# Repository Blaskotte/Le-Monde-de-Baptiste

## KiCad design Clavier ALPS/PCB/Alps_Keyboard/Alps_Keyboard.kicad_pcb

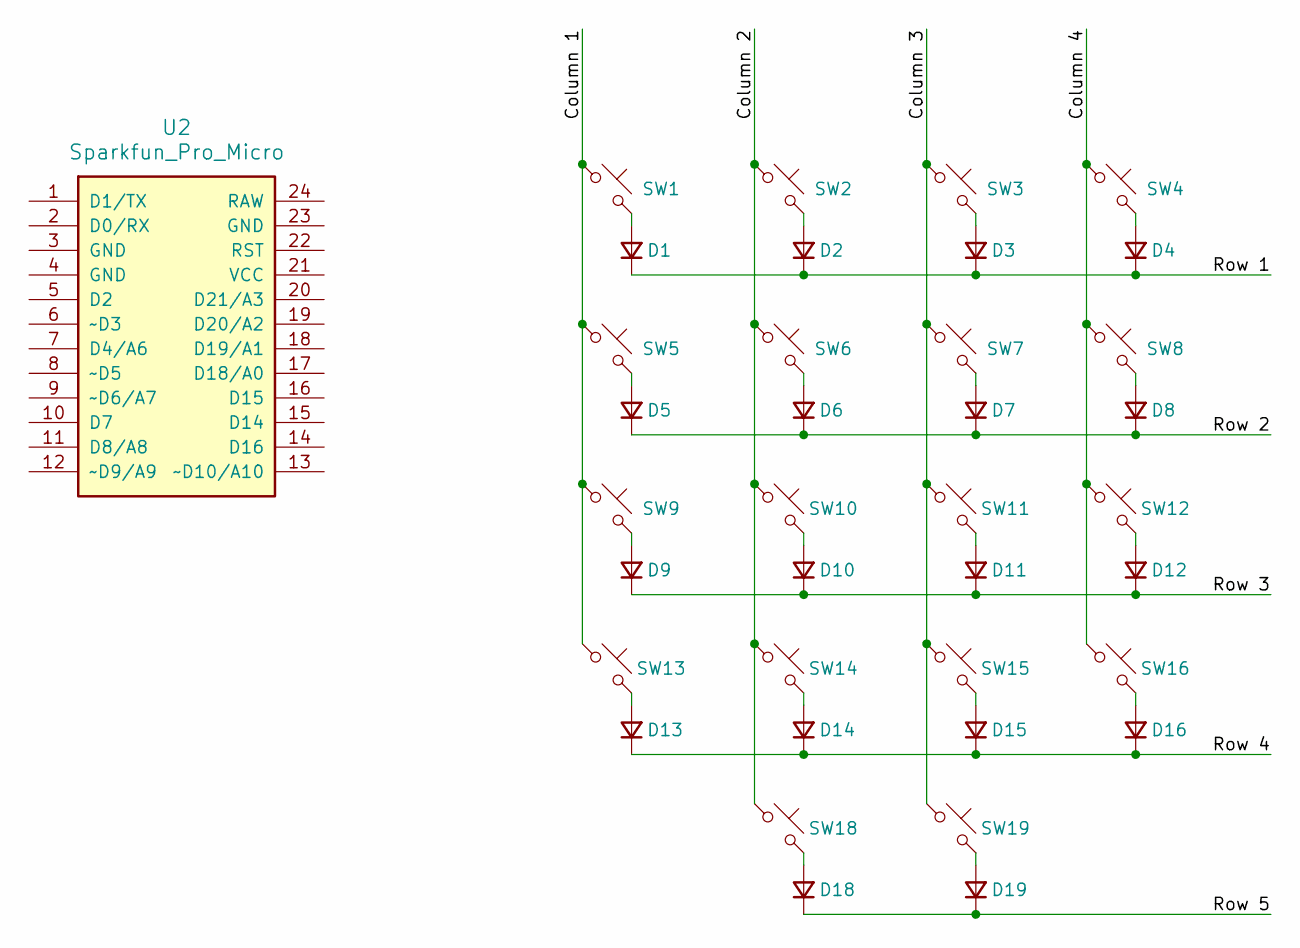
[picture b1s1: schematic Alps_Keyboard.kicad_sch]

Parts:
D1, D2, D3, D4, D5, D6, D7, D8, D9, D10, D11, D12, D13, D14, D15, D16, D18, D19: D_Small; D_0805_2012Metric_Pad1.15x1.40mm_HandSolder
SW1, SW2, SW3, SW4, SW5, SW6, SW7, SW8, SW9, SW10, SW11, SW12, SW13, SW14, SW15, SW16, SW18, SW19: SW_Push_45deg; Alps-Solderable-1U
U2: Sparkfun_Pro_Micro

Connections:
/Column 1: SW1.1, SW5.1, SW9.1, SW13.1
/Column 2: SW2.1, SW6.1, SW10.1, SW14.1, SW18.1
/Column 3: SW3.1, SW7.1, SW11.1, SW15.1, SW19.1
/Column 4: SW4.1, SW8.1, SW12.1, SW16.1
/Row 1: D1.1 (K), D2.1 (K), D3.1 (K), D4.1 (K)
/Row 2: D5.1 (K), D6.1 (K), D7.1 (K), D8.1 (K)
/Row 3: D9.1 (K), D10.1 (K), D11.1 (K), D12.1 (K)
/Row 4: D13.1 (K), D14.1 (K), D15.1 (K), D16.1 (K)
/Row 5: D18.1 (K), D19.1 (K)
unnamed: D1.2 (A), SW1.2
unnamed: D2.2 (A), SW2.2
unnamed: D3.2 (A), SW3.2
unnamed: D4.2 (A), SW4.2
unnamed: D5.2 (A), SW5.2
unnamed: D6.2 (A), SW6.2
unnamed: D7.2 (A), SW7.2
unnamed: D8.2 (A), SW8.2
unnamed: D9.2 (A), SW9.2
unnamed: D10.2 (A), SW10.2
unnamed: D11.2 (A), SW11.2
unnamed: D12.2 (A), SW12.2
unnamed: D13.2 (A), SW13.2
unnamed: D14.2 (A), SW14.2
unnamed: D15.2 (A), SW15.2
unnamed: D16.2 (A), SW16.2
unnamed: D18.2 (A), SW18.2
unnamed: D19.2 (A), SW19.2

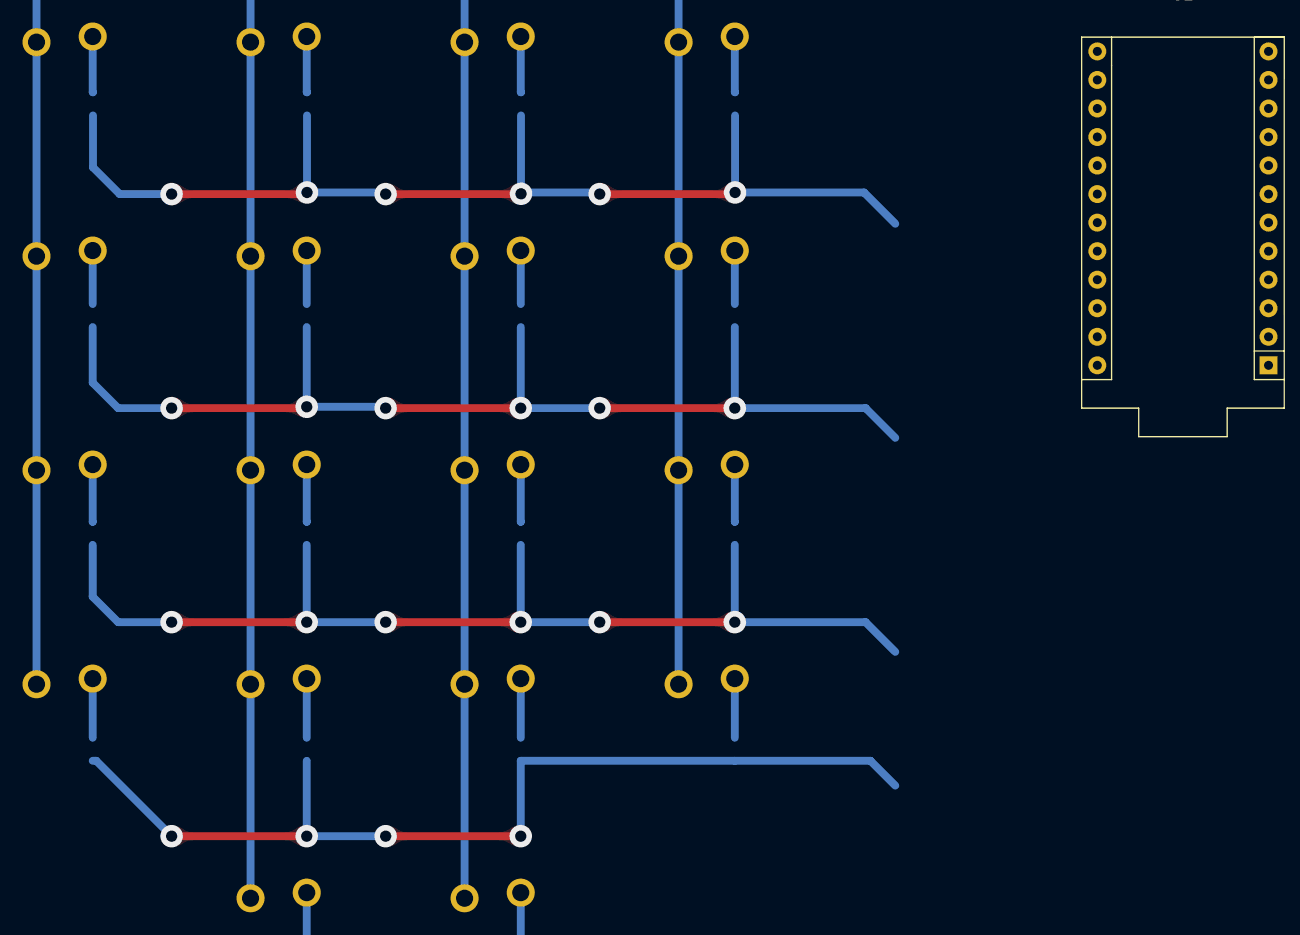
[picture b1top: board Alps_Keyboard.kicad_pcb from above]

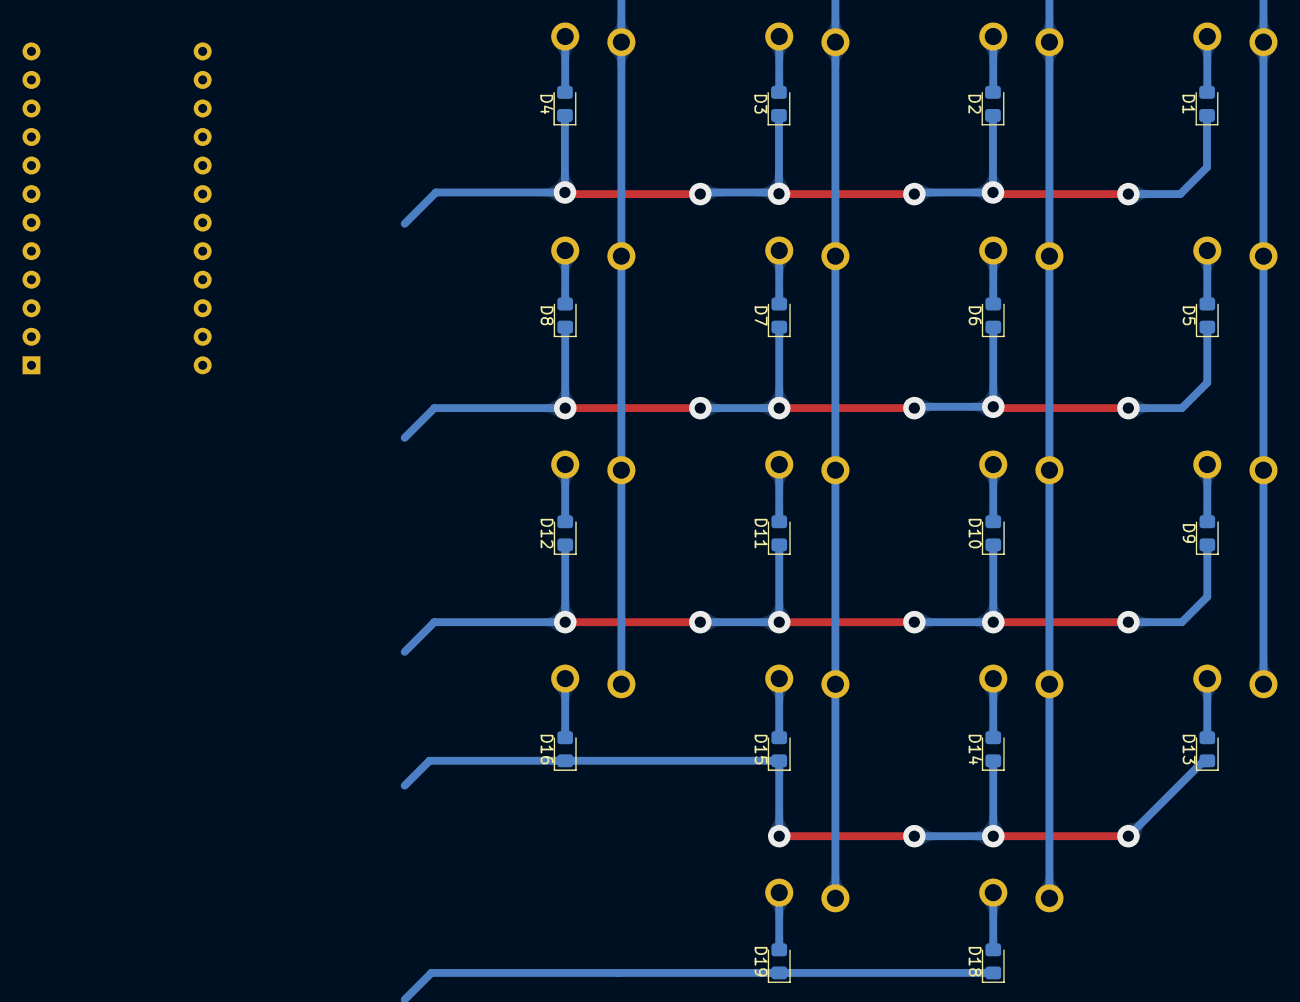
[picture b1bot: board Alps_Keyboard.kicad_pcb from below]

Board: 2 copper layers, 37 parts (18 on the bottom side), 27 nets.

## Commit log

2025-01-15 Beta 1.0
    Première Beta de l'alarme au style Sims 2
2025-01-16 Update Programme_ALARME.ino
    Ajout de la séquence avant l'armement de l'alarme
2025-01-16 Add inspiration files
2025-01-16 Add messages
2025-01-16 New Keypad
    I made a numeric keypad that has the same layout as the final keypad. I also modified the code to make the new keypad functional.
2025-01-16 Update Programme_ALARME.ino
    Code clean-up.
2025-01-16 Update Programme_ALARME.ino
    Settings button can now return to the main menu when pressed.
2025-01-17 Change password capacity
    It's now possible to change the password in the settings
2025-01-17 Beta 2.0
    The program can now fully operate. Looking for any bugs that might occur.
2025-01-17 Modify the goal
2025-01-17 Moved files
2025-01-17 Alarme 2003 - 1.0
    First official version of the 2003 Security Alarm.
2025-01-17 Alarme 2003 - 1.0
    First official version of the "Alarme 2003".
2025-01-26 International code update
    The original code has been updated to be entirely in English to avoid any confusion with French words.
    This update paves the way for a future language update that will allow users to choose from several languages when using Alarme 2003.
2025-01-27 Update Programme_ALARME.ino
    - Start adding options in English. (startup sequence is now bilingual)
    - =====Alarme===== is now ===Alarme2003===
2025-02-10 Added some files for different projects
2025-02-10 Some test
2025-02-10 Added interface mockup file
2025-02-10 New name, more clarity
2025-02-11 New file for display ressources
2025-02-11 Added icons for the main interface
2025-02-11 Modify
2025-02-11 First sketch of the main menu has been done
2025-02-12 Ignore
2025-02-12 Update MorningClockApp.ino
    Added Splash screen, button, MP3 player
2025-02-13 added first sounds effects
2025-02-13 Updated alarmON_select icon
2025-02-13 Update MorningClockApp.ino
    Finally, you can navigate through the home page
2025-02-13 Improved version of some icons
2025-02-13 Added new icons
2025-02-13 Settings menu added
2025-02-14 Deleted useless files
2025-02-16 Alarm settings menu is done
2025-02-18 Prototype n°1 update
    I've made the first prototype of the morning clock and here's the version of the program I'm going to include.
2025-02-20 Update MorningClockApp.ino
    The software is now fully functional. The next step will be to improve readability and resolve a few bugs.
2025-02-23 Added animations
2025-02-26 Migrate from arduino to ESP32
2025-02-28 Update MorningClockESP32.ino
    new design for menus, added scroll bar
2025-03-04 BETA 2.1.1
    Improved the way to display the scrollbar
2025-03-04 BETA 2.1.15
    Display menu added
2025-03-07 BETA 2.1.2
    Display menu + new animations
2025-03-08 BETA 2.2
    The clock and date can now be set
2025-03-18 BETA 2.2.5
    mainly debugging and repairs
2025-04-04 New way of sorting files
2025-04-11 BETA 3.0
    New 128x96 pixel screen
2025-04-13 BETA 3.1
    Added the function that lets you choose your alarm clock music
2025-04-15 BETA 3.2
2025-04-22 Update
    The project has been moved to a new repo for greater clarity.
2026-01-23 Added new project
2026-01-24 Main menu working
2026-01-24 added some features
2026-01-24 Added first version of followLineMode
2026-01-25 final version
2026-01-29 robotic day
2026-04-15 New project (Alps keypad)
